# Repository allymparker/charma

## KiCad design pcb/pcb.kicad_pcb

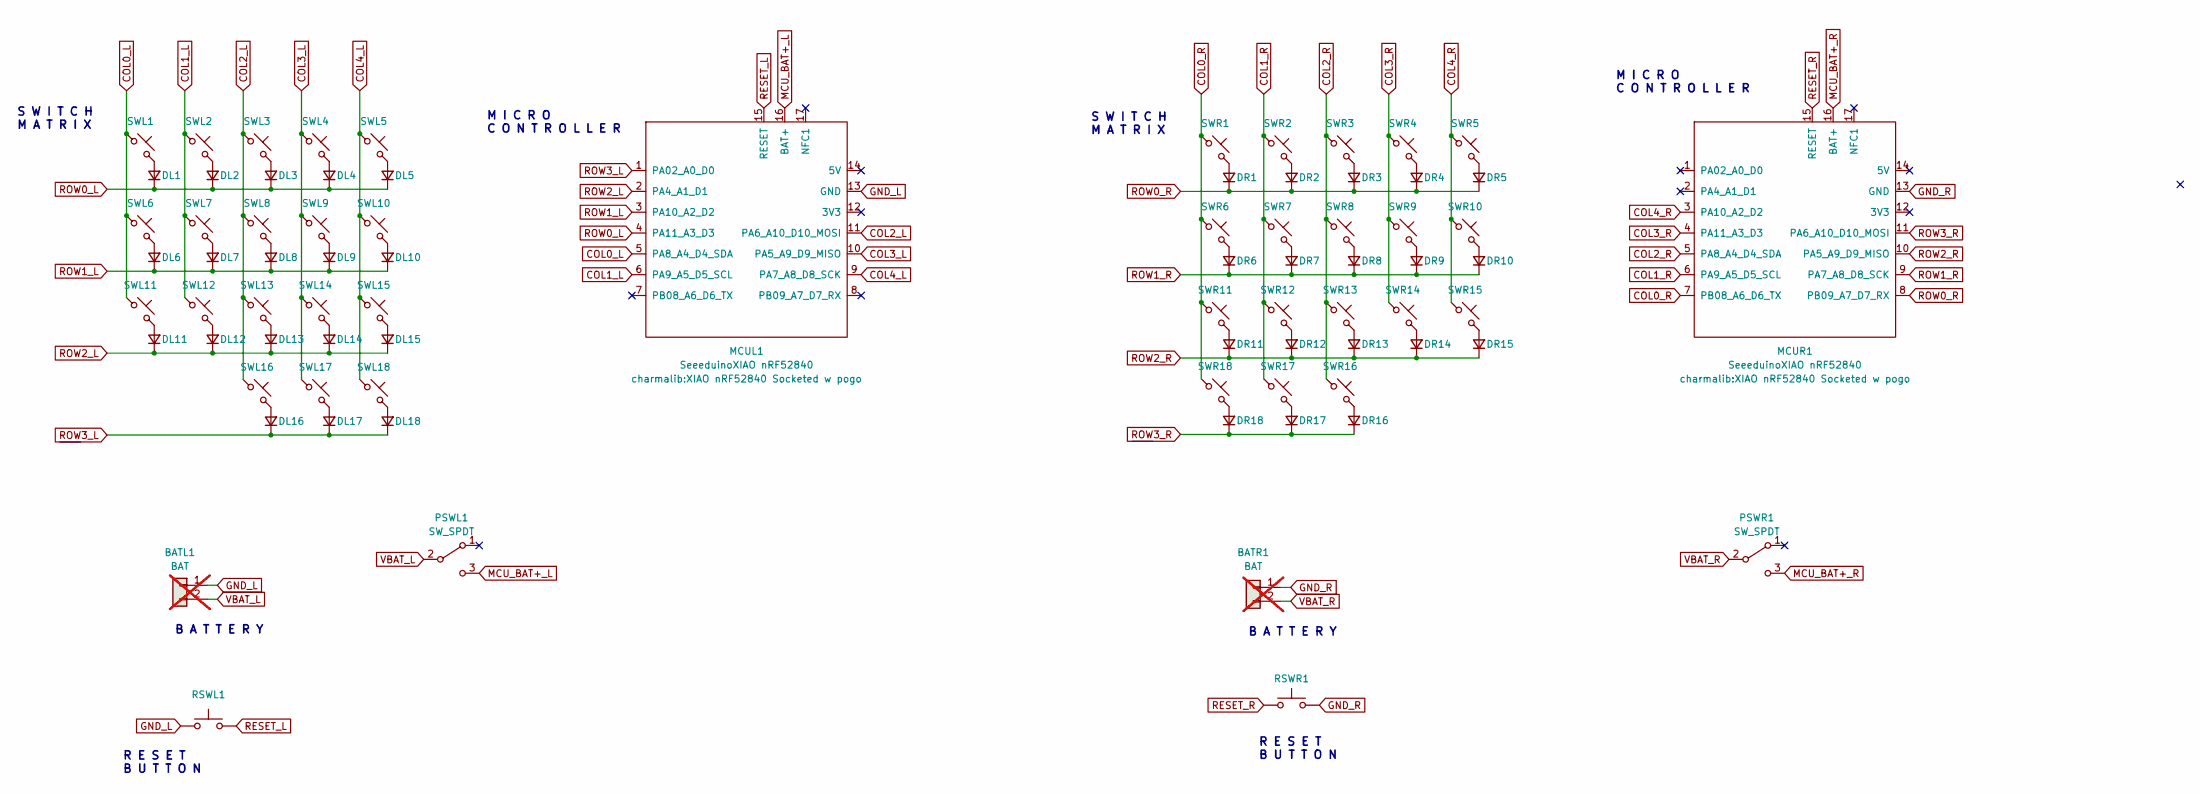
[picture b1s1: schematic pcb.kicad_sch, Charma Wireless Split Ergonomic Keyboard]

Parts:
BATL1: BAT; PinHeader_1x02_P2.54mm_Vertical; not fitted
BATR1: BAT; PinHeader_1x02_P2.54mm_Vertical; not fitted
DL1, DL2, DL3, DL4, DL5, DL6, DL7, DL8, DL9, DL10, DL11, DL12, DL13, DL14, DL15, DL16, DL17, DL18: D_Small; Diode_SOD123
DR1, DR2, DR3, DR4, DR5, DR6, DR7, DR8, DR9, DR10, DR11, DR12, DR13, DR14, DR15, DR16, DR17, DR18: D_Small; Diode_SOD123
MCUL1: SeeeduinoXIAO nRF52840; XIAO nRF52840 Socketed w pogo
MCUR1: SeeeduinoXIAO nRF52840; XIAO nRF52840 Socketed w pogo
PSWL1: SW_SPDT; SW_SPDT_PCM12
PSWR1: SW_SPDT; SW_SPDT_PCM12
RSWL1: SW_Push; SW_SPST_SKQG_WithStem
RSWR1: SW_Push; SW_SPST_SKQG_WithStem
SWL1, SWL2, SWL3, SWL4, SWL5, SWL6, SWL7, SWL8, SWL9, SWL10, SWL11, SWL12, SWL13, SWL14, SWL15, SWL16, SWL17, SWL18: SW_Push_45deg; Kailh_Socket_PG1350_Optional
SWR1, SWR2, SWR3, SWR4, SWR5, SWR6, SWR7, SWR8, SWR9, SWR10, SWR11, SWR12, SWR13, SWR14, SWR15, SWR16, SWR17, SWR18: SW_Push_45deg; Kailh_Socket_PG1350_Optional

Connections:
COL0_L: MCUL1.5 (PA8_A4_D4_SDA), SWL1.1, SWL6.1, SWL11.1
COL0_R: MCUR1.7 (PB08_A6_D6_TX), SWR1.1, SWR6.1, SWR11.1, SWR18.1
COL1_L: MCUL1.6 (PA9_A5_D5_SCL), SWL2.1, SWL7.1, SWL12.1
COL1_R: MCUR1.6 (PA9_A5_D5_SCL), SWR2.1, SWR7.1, SWR12.1, SWR17.1
COL2_L: MCUL1.11 (PA6_A10_D10_MOSI), SWL3.1, SWL8.1, SWL13.1, SWL16.1
COL2_R: MCUR1.5 (PA8_A4_D4_SDA), SWR3.1, SWR8.1, SWR13.1, SWR16.1
COL3_L: MCUL1.10 (PA5_A9_D9_MISO), SWL4.1, SWL9.1, SWL14.1, SWL17.1
COL3_R: MCUR1.4 (PA11_A3_D3), SWR4.1, SWR9.1, SWR14.1
COL4_L: MCUL1.9 (PA7_A8_D8_SCK), SWL5.1, SWL10.1, SWL15.1, SWL18.1
COL4_R: MCUR1.3 (PA10_A2_D2), SWR5.1, SWR10.1, SWR15.1
GND_L: BATL1.1, MCUL1.13 (GND), RSWL1.1
GND_R: BATR1.1, MCUR1.13 (GND), RSWR1.2
MCU_BAT+_L: MCUL1.16 (BAT+), PSWL1.3 (C)
MCU_BAT+_R: MCUR1.16 (BAT+), PSWR1.3 (C)
unnamed: DL1.2 (A), SWL1.2
unnamed: DL2.2 (A), SWL2.2
unnamed: DL3.2 (A), SWL3.2
unnamed: DL4.2 (A), SWL4.2
unnamed: DL5.2 (A), SWL5.2
unnamed: DL6.2 (A), SWL6.2
unnamed: DL7.2 (A), SWL7.2
unnamed: DL8.2 (A), SWL8.2
unnamed: DL9.2 (A), SWL9.2
unnamed: DL10.2 (A), SWL10.2
unnamed: DL11.2 (A), SWL11.2
unnamed: DL12.2 (A), SWL12.2
unnamed: DL13.2 (A), SWL13.2
unnamed: DL14.2 (A), SWL14.2
unnamed: DL15.2 (A), SWL15.2
unnamed: DL16.2 (A), SWL16.2
unnamed: DL17.2 (A), SWL17.2
unnamed: DL18.2 (A), SWL18.2
unnamed: DR1.2 (A), SWR1.2
unnamed: DR2.2 (A), SWR2.2
unnamed: DR3.2 (A), SWR3.2
unnamed: DR4.2 (A), SWR4.2
unnamed: DR5.2 (A), SWR5.2
unnamed: DR6.2 (A), SWR6.2
unnamed: DR7.2 (A), SWR7.2
unnamed: DR8.2 (A), SWR8.2
unnamed: DR9.2 (A), SWR9.2
unnamed: DR10.2 (A), SWR10.2
unnamed: DR11.2 (A), SWR11.2
unnamed: DR12.2 (A), SWR12.2
unnamed: DR13.2 (A), SWR13.2
unnamed: DR14.2 (A), SWR14.2
unnamed: DR15.2 (A), SWR15.2
unnamed: DR16.2 (A), SWR16.2
unnamed: DR17.2 (A), SWR17.2
unnamed: DR18.2 (A), SWR18.2
RESET_L: MCUL1.15 (RESET), RSWL1.2
RESET_R: MCUR1.15 (RESET), RSWR1.1
ROW0_L: DL1.1 (K), DL2.1 (K), DL3.1 (K), DL4.1 (K), DL5.1 (K), MCUL1.4 (PA11_A3_D3)
ROW0_R: DR1.1 (K), DR2.1 (K), DR3.1 (K), DR4.1 (K), DR5.1 (K), MCUR1.8 (PB09_A7_D7_RX)
ROW1_L: DL6.1 (K), DL7.1 (K), DL8.1 (K), DL9.1 (K), DL10.1 (K), MCUL1.3 (PA10_A2_D2)
ROW1_R: DR6.1 (K), DR7.1 (K), DR8.1 (K), DR9.1 (K), DR10.1 (K), MCUR1.9 (PA7_A8_D8_SCK)
ROW2_L: DL11.1 (K), DL12.1 (K), DL13.1 (K), DL14.1 (K), DL15.1 (K), MCUL1.2 (PA4_A1_D1)
ROW2_R: DR11.1 (K), DR12.1 (K), DR13.1 (K), DR14.1 (K), DR15.1 (K), MCUR1.10 (PA5_A9_D9_MISO)
ROW3_L: DL16.1 (K), DL17.1 (K), DL18.1 (K), MCUL1.1 (PA02_A0_D0)
ROW3_R: DR16.1 (K), DR17.1 (K), DR18.1 (K), MCUR1.11 (PA6_A10_D10_MOSI)
VBAT_L: BATL1.2, PSWL1.2 (B)
VBAT_R: BATR1.2, PSWR1.2 (B)

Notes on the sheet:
S W I T C H M A T R I X
M I C R O C O N T R O L L E R
B A T T E R Y
R E S E T B U T T O N

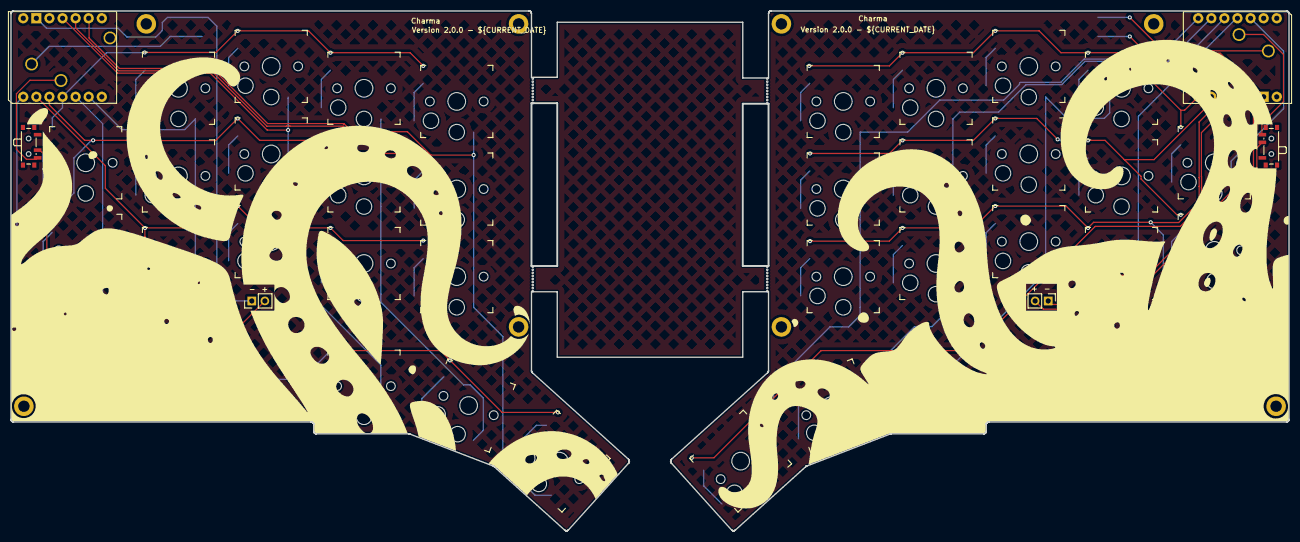
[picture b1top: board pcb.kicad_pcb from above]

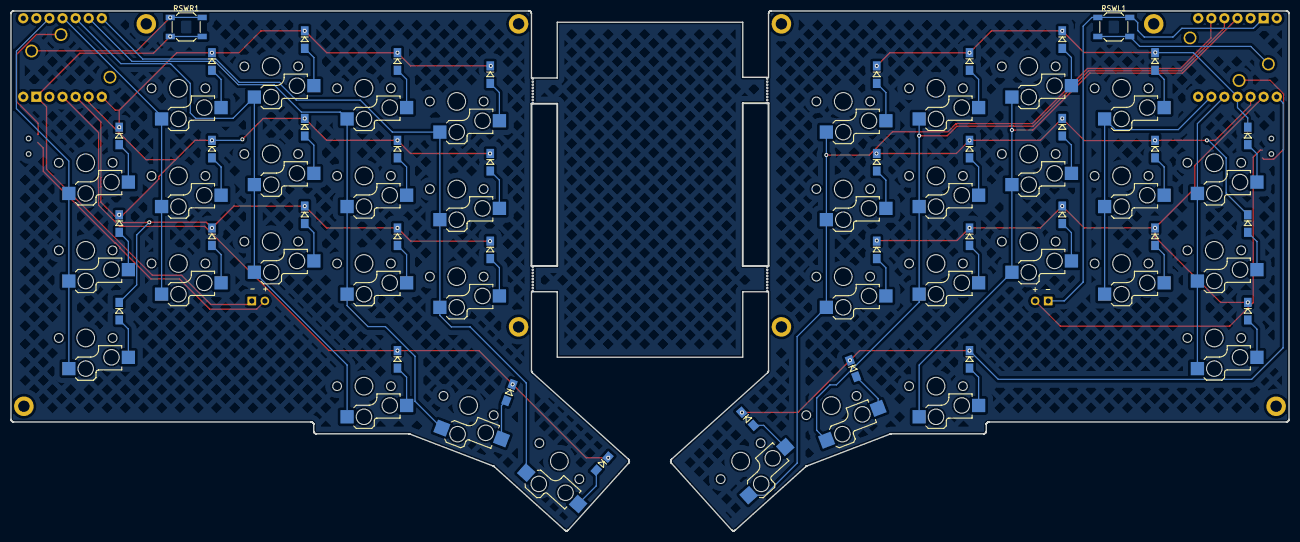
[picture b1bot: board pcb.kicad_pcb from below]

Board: 2 copper layers, 248.0 x 100.9 mm, 88 parts (38 on the bottom side), 62 nets.

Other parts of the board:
HOLEL1, HOLEL2, HOLEL3, HOLEL4: MountingHole_2.2mm_M2_DIN965_Pad
HOLER1, HOLER2, HOLER3, HOLER4: MountingHole_2.2mm_M2_DIN965_Pad

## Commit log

2024-11-16 WIP Update switch spacing to choc
2024-11-18 Tracks
2024-11-18 Fixings
2024-12-08 Left V1
2024-12-14 Left Done
2024-12-14 Right Positioned
2024-12-14 ignore
2024-12-14 PCB v1
2025-07-10 Long overdue commit!
2025-07-12 v2 init
2025-07-12 rename to pcb
2025-07-12 rename to Charma
2025-07-16 Calc posns
2025-07-17 thumbs first attempt
2025-07-17 Revert "thumbs first attempt"
    This reverts commit 60ba6088ca17424da604f0f81e54bc2504407d9b.
2025-07-17 Name switches properly
2025-07-17 Mirror right from left
2025-07-17 Parameterise
2025-07-17 Use centers for coordinates
2025-07-17 Thumb arcs
2025-07-17 Put the thumbs in the right spot
2025-07-18 Switches working!
2025-07-18 add diodes
2025-07-18 Use code directly
2025-07-18 Use poisitoning code explicitly
2025-07-18 Update refs
2025-07-18 Add specific points
2025-07-19 Diode orientation
2025-07-19 update orientations
2025-07-26 Add origin offset to place inside edge cuts
2025-07-26 Change font
2025-07-27 Use SKQB for reset
2025-07-27 dynamic reload to pick up changes
2025-07-27 Postion tweaks to match edge cuts
2025-07-27 Move MCU closer to edge
2025-07-27 Pull out config
2025-07-27 Unit tests
2025-07-27 Update placement
2025-07-27 Remove old stuff
2025-07-27 simplify placement
2025-07-27 tweaks
2025-07-27 Fixup separation
2025-07-27 hairline
2025-07-29 Add switch plate svg
2025-07-29 Use svgwrite
2025-07-29 rename
2025-07-29 switch mounting holes
2025-07-29 Add hotswap profile
2025-07-29 Extract duplicate code
2025-07-29 format
2025-07-29 simplify svg size calcs
2025-07-29 make origin the same
2025-07-30 fix up task
2025-07-30 Cad dim clean up
2025-07-30 Add diode pills
2025-07-30 Fix hotswap thumb rotation
2025-07-30 Try an instruction
2025-07-30 Fix hotswap position
2025-07-30 Fix central switch recess size
2025-07-30 Code cleanup
2025-07-31 Move print_positions
2025-07-31 Use socketed Xiao
2025-08-01 Fix diodes
2025-08-01 add fixing holes
2025-08-03 combined edge cuts
    combined edge cuts
    combined edge cuts
2025-08-05 Add midline
2025-08-06 Update models
2025-08-06 Move up a level
2025-08-06 Fix new location
2025-08-09 Screw holes
2025-08-09 Update cuts
2025-08-10 Shift hotswap down .25mm
2025-08-10 Split bottom recesses and hotswaps
2025-08-12 Logo
2025-08-14 logos
2025-08-27 Position power switches
2025-08-31 Route and silkscreen
